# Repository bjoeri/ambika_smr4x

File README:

SMR4X - Mutated Ambika SMR-4 voice card

SMR4X is a mutation of the original Ambika SMR-4 voice card with an additional mash up of various other design modifications:
- Added programmable 4P/2P filter slope selection (ported from SMR-4-Pi but with added decoupling capacitors for the 4052 and excluding the 1P/3P slopes)
- Added programmable full bandwidth resonance compensation by optional bypass of capacitor in feedback (inspired by Shruthi-1 Sound Designer Edition). NOTE: FOR SOME REASON THIS DOESN'T APPEAR TO MAKE ANY SIGNIFICANT DIFFERENCE, SEE https://forum.mutable-instruments.net/t/another-modified-ambika-smr-4-voice-card/
- Added 50k trimpot and modified related resistor value (from 150k to 120k) to allow for filter tuning (ported from SMR4-Plus)

==============================================
WARNING: THIS IS INCOMPLETE WORKS IN PROGRESS! 
==============================================

SMR4X is released under cc-by-sa 4.0 license.

Original design of the official SMR4 voice card by E. Gillet (pichenettes@mutable-instruments.net).

This design by Björn Somell (bjoeri@gmail.com) relies heavily on the original design, and is inspired by modifications from SMR-4-Pi voice card by Pharmasonic (https://github.com/Pharmasonic/SMR-4-Pi), Shruthi-1 Sound Designer Edition by Martin Walkers (http://mutable-instruments-archive.net/wiki/Shruthi-1_SDE), and SMR4-Plus voice card by Andre Laska (kontakt@tubeohm.com)

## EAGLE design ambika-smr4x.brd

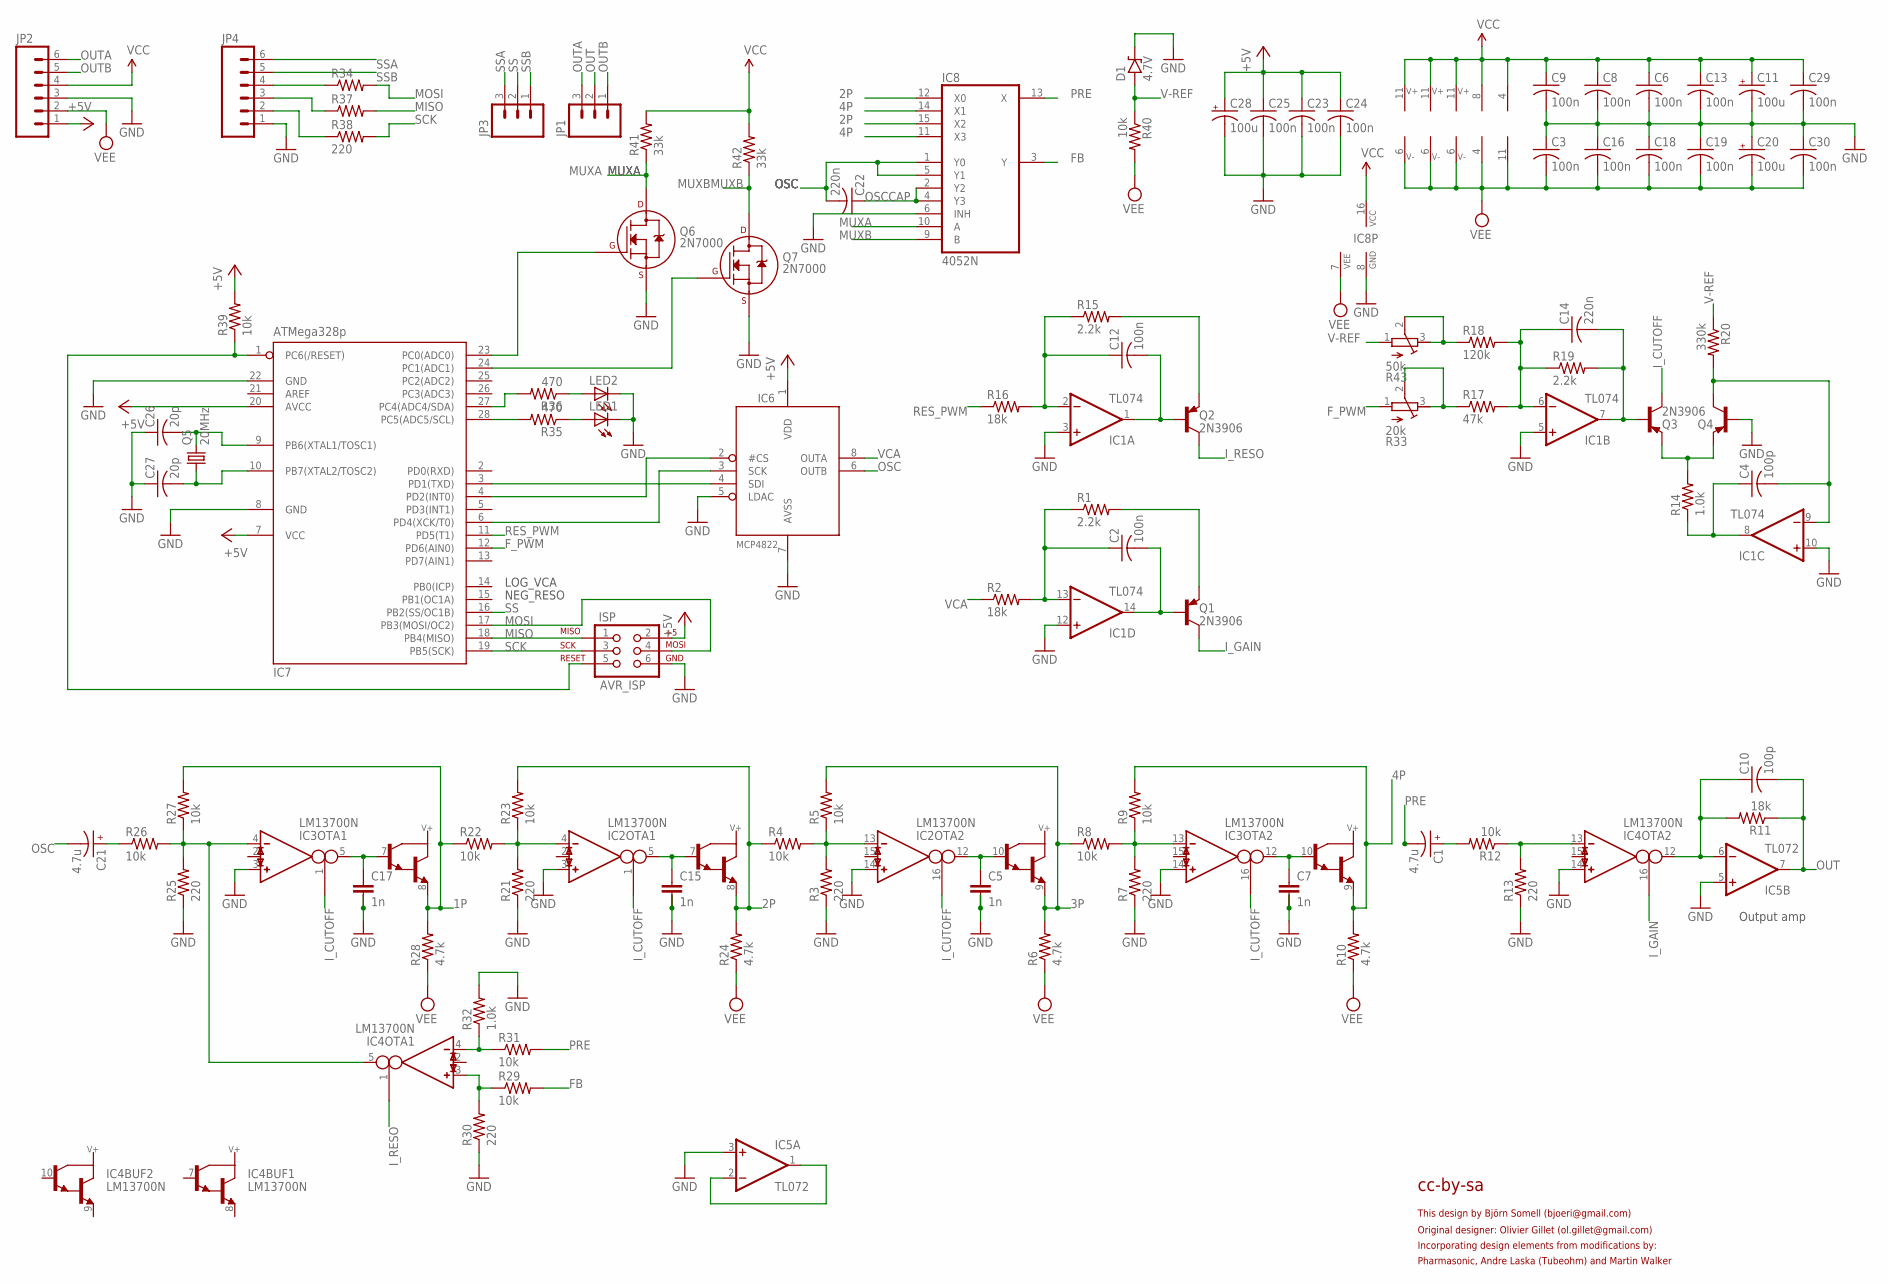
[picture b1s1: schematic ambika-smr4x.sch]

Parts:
C1, C21: 4.7u; E11-6.3
C2, C3, C6, C8, C9, C12, C13, C16, C18, C19, C23, C24, C29, C30: 100n; C025-025X050
C4, C10: 100p; C025-025X050
C5, C7, C15, C17: 1n; C2.5/5-2
C11, C20, C28: 100u; E2,5-6
C14, C22: 220n; C025-025X050
C25: 100n; C025-024X044
C26, C27: 20p; C025-024X044
D1: 4.7V; D-5
IC1: TL074; DIL14
IC2, IC3, IC4: LM13700N; DIL16
IC5: TL072; DIL08
IC6: MCP4822; DIL08
IC7: ATMega328p; DIL28-3
IC8: 4052N; DIL16
ISP: AVR_ISP; 2X3
JP1, JP3: M03PTH; 1X03
JP2, JP4: M06SIP; 1X06
LED1, LED2: LED3MM
Q1, Q2, Q3, Q4: 2N3906; TO92-
Q5: 20MHz; HC49U-V
Q6, Q7: 2N7000; TO-92
R1, R15, R19: 2.2k; 0204/7
R2, R11, R16: 18k; 0204/7
R3, R7, R13, R21, R25, R30, R34, R37, R38: 220; 0204/7
R4, R5, R8, R9, R12, R22, R23, R26, R27, R29, R31, R39, R40: 10k; 0204/7
R6, R10, R24, R28: 4.7k; 0204/7
R14, R32: 1.0k; 0204/7
R17: 47k; 0204/7
R18: 120k; 0204/7
R20: 330k; 0204/7
R33: 20k; RTRIM3296P
R35, R36: 470; 0204/7
R41, R42: 33k; 0204/7
R43: 50k; RTRIM3296P

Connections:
1P: IC3.8 (E), R22.1, R27.2, R28.2
2P: IC2.8 (E), IC8.12 (X0), IC8.15 (X2), R4.1, R23.2, R24.2
3P: IC2.9 (E), R5.2, R6.2, R8.1
4P: IC3.9 (E), IC8.11 (X3), IC8.14 (X1), R9.2, R10.2
+5V: C23.1, C24.1, C25.1, C28.+, IC6.1 (VDD), IC7.7 (VCC), IC7.20 (AVCC), ISP.2, JP2.1, R39.2
FB: IC8.3 (Y), R29.2
F_PWM: IC7.12 (PD6(AIN0)), R33.1 (E)
GND: C3.1, C5.2, C5.3, C6.2, C7.2, C7.3, C8.2, C9.2, C11.-, C13.2, C15.2, C15.3, C16.1, C17.2, C17.3, C18.1, C19.1, C20.+, C23.2, C24.2, C25.2, C26.1, C27.1, C28.-, C29.2, C30.1, D1.C, IC1.3 (+IN), IC1.5 (+IN), IC1.10 (+IN), IC1.12 (+IN), IC2.3 (IN_P), IC2.14 (IN_P), IC3.3 (IN_P), IC3.14 (IN_P), IC4.14 (IN_P), IC5.3 (+IN), IC5.5 (+IN), IC6.5 (LDAC), IC6.7 (AVSS), IC7.8 (GND), IC7.22 (GND), IC8.6 (INH), IC8.8 (GND), ISP.6, JP2.3, JP4.1, LED1.K (C), LED2.K (C), Q4.2 (B), Q6.1 (S), Q7.1 (S), R3.1, R7.1, R13.1, R21.1, R25.1, R30.1, R32.2
I_CUTOFF: IC2.1 (I_BIAS), IC2.16 (I_BIAS), IC3.1 (I_BIAS), IC3.16 (I_BIAS), Q3.1 (C)
I_GAIN: IC4.16 (I_BIAS), Q1.1 (C)
I_RESO: IC4.1 (I_BIAS), Q2.1 (C)
MISO: IC7.18 (PB4(MISO)), ISP.1, R37.2
MOSI: IC7.17 (PB3(MOSI/OC2)), ISP.4, R34.2
MUXA: IC8.10 (A), Q6.3 (D), R41.1
MUXB: IC8.9 (B), Q7.3 (D), R42.1
unnamed: Q3.3 (E), Q4.3 (E), R14.2
unnamed: C14.2, IC1.7 (OUT), Q3.2 (B), R19.2
unnamed: IC6.4 (SDI), IC7.3 (PD1(TXD))
unnamed: C4.2, IC1.9 (-IN), Q4.1 (C), R20.2
unnamed: C21.+ (1), R26.1
unnamed: R18.1, R43.2 (S), R43.3 (A)
unnamed: LED1.A, R35.1
unnamed: JP4.2, R38.1
unnamed: C4.1, IC1.8 (OUT), R14.1
unnamed: LED2.A, R36.1
unnamed: IC7.27 (PC4(ADC4/SDA)), R36.2
unnamed: IC3.4 (IN_N), IC4.5 (OUT), R25.2, R26.2, R27.1
unnamed: JP4.3, R37.1
unnamed: IC7.1 (PC6(/RESET)), ISP.5, R39.1
unnamed: IC6.3 (SCK), IC7.6 (PD4(XCK/T0))
unnamed: IC6.2 (#CS), IC7.4 (PD2(INT0))
unnamed: IC2.4 (IN_N), R21.2, R22.2, R23.1
unnamed: JP4.4, R34.1
unnamed: C15.1, IC2.5 (OUT), IC2.7 (B)
unnamed: IC7.28 (PC5(ADC5/SCL)), R35.2
unnamed: IC2.13 (IN_N), R3.2, R4.2, R5.1
unnamed: IC5.1 (OUT), IC5.2 (-IN)
unnamed: C5.1, IC2.10 (B), IC2.12 (OUT)
unnamed: IC3.13 (IN_N), R7.2, R8.2, R9.1
unnamed: IC7.23 (PC0(ADC0)), Q6.2 (G)
unnamed: C1.+ (1), R12.2
unnamed: C7.1, IC3.10 (B), IC3.12 (OUT)
unnamed: IC4.4 (IN_N), R31.1, R32.1
unnamed: C12.2, IC1.1 (OUT), Q2.2 (B)
unnamed: C2.2, IC1.14 (OUT), Q1.2 (B)
unnamed: IC4.3 (IN_P), R29.1, R30.2
unnamed: IC4.13 (IN_N), R12.1, R13.2
unnamed: IC7.24 (PC1(ADC1)), Q7.2 (G)
unnamed: C14.1, IC1.6 (-IN), R17.2, R18.2, R19.1
unnamed: R17.1, R33.2 (S), R33.3 (A)
unnamed: C2.1, IC1.13 (-IN), R1.1, R2.2
unnamed: C12.1, IC1.2 (-IN), R15.1, R16.2
unnamed: Q2.3 (E), R15.2
unnamed: C17.1, IC3.5 (OUT), IC3.7 (B)
unnamed: Q1.3 (E), R1.2
unnamed: C10.1, IC4.12 (OUT), IC5.6 (-IN), R11.2
unnamed: C27.2, IC7.10 (PB7(XTAL2/TOSC2)), Q5.1
unnamed: C26.2, IC7.9 (PB6(XTAL1/TOSC1)), Q5.2
OSC: C21.- (2), C22.2, IC6.6 (OUTB), IC8.1 (Y0), IC8.5 (Y1)
OSCCAP: C22.1, IC8.2 (Y2), IC8.4 (Y3)
OUT: C10.2, IC5.7 (OUT), JP1.2, R11.1
OUTA: JP1.3, JP2.6
OUTB: JP1.1, JP2.5
PRE: C1.- (2), IC8.13 (X), R31.2
RES_PWM: IC7.11 (PD5(T1)), R16.1
SCK: IC7.19 (PB5(SCK)), ISP.3, R38.2
SS: IC7.16 (PB2(SS/OC1B)), JP3.2
SSA: JP3.3, JP4.6
SSB: JP3.1, JP4.5
V-REF: D1.A, R20.1, R40.1, R43.1 (E)
VCA: IC6.8 (OUTA), R2.1
VCC: C6.1, C8.1, C9.1, C11.+, C13.1, C29.1, IC1.4 (V+), IC2.11 (V+), IC3.11 (V+), IC4.11 (V+), IC5.8 (V+), IC8.16 (VCC), JP2.4, R41.2, R42.2
VEE: C3.2, C16.2, C18.2, C19.2, C20.-, C30.2, IC1.11 (V-), IC2.6 (V-), IC3.6 (V-), IC4.6 (V-), IC5.4 (V-), IC8.7 (VEE), JP2.2, R6.1, R10.1, R24.1, R28.1, R40.2

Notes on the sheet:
cc-by-sa
This design by Björn Somell (bjoeri@gmail.com)
LOG_VCA
NEG_RESO
Output amp
Original designer: Olivier Gillet (ol.gillet@gmail.com)
Incorporating design elements from modifications by:
Pharmasonic, Andre Laska (Tubeohm) and Martin Walker

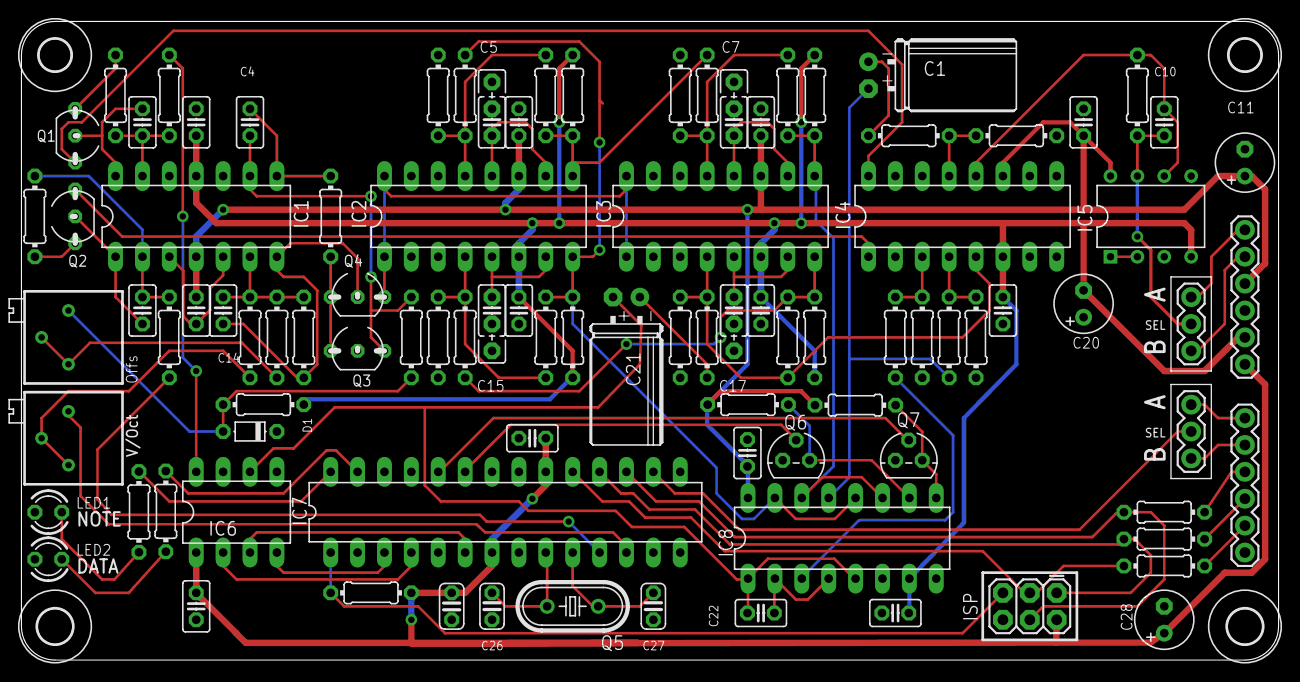
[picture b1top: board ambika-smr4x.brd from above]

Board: 2 copper layers, 118.7 x 60.3 mm, 100 parts (0 on the bottom side), 73 nets.

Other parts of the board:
U$1, U$2: 3,0
U$4, U$5: 3,3

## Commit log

2018-05-10 :confetti_ball: Added .gitattributes & .gitignore files
2018-05-13 Tidied up board (mainly routing and silkscreen)
2019-03-02 Updated README with status of this WIP
    Updated README with status of this works-in-progress
2020-03-23 Updated original designer etc info in schematics
    Updated original designer etc info in schematics
